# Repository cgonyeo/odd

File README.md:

odd
===

One Dimensional Display

http://blog.gonyeo.com/category/odd.html

This project aims to create a single row of RGB LEDs that can be individually 
controlled by a Raspberry Pi. The Pi will be able to display single colors, 
basic hardcoded animations, dynamic animations (like audio visualization), and 
animations in reaction to various events (like someone entered a room, or the 
user reveived a message on Facebook).

The hardware will consist of packages of one TLC5947, eight RGB LEDs, one 
voltage regulator, and some capacitors and resistors on a PCB. These circuit 
boards will be daisy chainable, with an end goal of about 30 boards (240 LEDs).

The hardware will be controlled in roughly the following fashion:

HTML/CSS/Javascript ---> C ---> TLC5947 ---> LEDs

Here's an imcomplete parts list:
 - Raspberry Pi
 - TLC5947 (LED Driver)
 - RGB LEDs (8x the # of TLCs)
 - One of the PCBs from the eagle board folder for each TLC
 - Resistors & capacitors
 - LM3940 (Voltage Regulator)

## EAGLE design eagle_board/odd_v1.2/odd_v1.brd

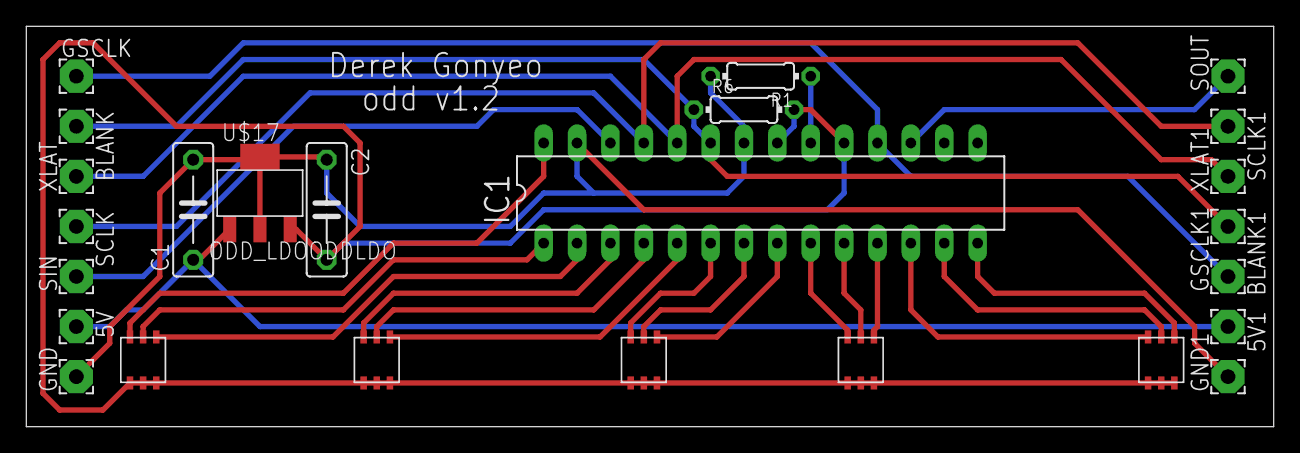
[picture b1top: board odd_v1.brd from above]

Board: 2 copper layers, 94.9 x 30.5 mm, 25 parts (0 on the bottom side), 25 nets.

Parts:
5V, 5V1: 2,54/1,1
BLANK, BLANK1: 2,54/1,1
C1, C2: C075-032X103
GND, GND1: 2,54/1,1
GSCLK, GSCLK1: 2,54/1,1
IC1: DIP28
R1, R6: 0204/7
SCLK, SCLK1: 2,54/1,1
SIN: 2,54/1,1
SOUT: 2,54/1,1
U$1, U$2, U$3, U$4, U$5: RGBLED; 6PADSMD
U$17: ODD_LDOODDLDO; 4PINLDO
XLAT, XLAT1: 2,54/1,1

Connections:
unnamed: IC1.28, U$1.B-
unnamed: IC1.1, U$1.G-
unnamed: IC1.2, U$1.R-
unnamed: IC1.3, U$2.B-
unnamed: IC1.4, U$2.G-
unnamed: IC1.5, U$2.R-
unnamed: IC1.6, U$3.B-
unnamed: IC1.7, U$3.G-
unnamed: IC1.8, U$3.R-
unnamed: IC1.26, SIN.1
unnamed: IC1.14, U$5.R-
unnamed: IC1.13, U$5.G-
unnamed: IC1.12, U$5.B-
unnamed: IC1.11, U$4.R-
unnamed: IC1.10, U$4.G-
unnamed: IC1.9, U$4.B-
unnamed: IC1.25, SCLK.1, SCLK1.1
unnamed: 5V.1, 5V1.1, C1.1, U$17.INPUT
unnamed: C1.2, C2.1, GND.1, GND1.1, IC1.22, IC1.27, R1.2, U$17.GND, U$17.GND2
unnamed: IC1.24, XLAT.1, XLAT1.1
unnamed: GSCLK.1, GSCLK1.1, IC1.18
unnamed: C2.2, IC1.19, IC1.21, R6.2, U$1.B+, U$1.G+, U$1.R+, U$2.B+, U$2.G+, U$2.R+, U$3.B+, U$3.G+, U$3.R+, U$4.B+, U$4.G+, U$4.R+, U$5.B+, U$5.G+, U$5.R+, U$17.OUTPUT
unnamed: IC1.17, SOUT.1
unnamed: BLANK.1, BLANK1.1, IC1.23, R6.1
unnamed: IC1.20, R1.1

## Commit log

2013-02-17 Initial commit. Proof of concept, arduino receives information from computer and updates LEDs to show a basic animation.
2013-02-17 Added an incomplete eagle board.
2013-02-17 Updated board, all desired connections in schematic have been made.
2013-02-18 Schematic modified to only have one TLC590, board made.
2013-02-18 Label added to board.
2013-02-18 Small changes.
2013-02-18 Made the cylonEye animation smoother
2013-02-18 Modified board, there were accidental and dumb connections being made. Also added two capacitors for use with the voltage regulator.
2013-02-19 Modified code to function with two Tlc5940s. Need to add capacitors to prevent decoupling issues to circuit, and then switch back off of bit banging to talk to the ics
2013-02-19 Added a strobe method
2013-02-19 Added threading support and fixed a potential bug with the serial writing. Baud rate also halved.
2013-02-19 LEDs were off by two. Fixed it. Not sure why that was happening or why my fix fixed it, but it fixed it.
2013-02-19 An LED wasn't updating because I told it not to. Removed the code that was doing that.
2013-02-19 Added ability for user input
2013-02-27 Made removing process easier (had to hit enter too many times). Also renamed file.
2013-02-27 Fixed stuff, added smoothStrobe animation
2013-02-27 Updated the board
2013-02-27 Added some animations
2013-02-28 Added initial color support. Not yet available to user.
2013-03-04 Added an inverse subtract, and fixed bug causing segmentation faults when the arduino is unplugged than the program is exited.
2013-03-05 Added a sin animation
2013-03-27 This commit might break lots of stuff. Need to back it up though.
2013-03-30 Full color support added, some animations appear broken.
2013-03-30 Color support fully functional
2013-04-01 C driver has been split up into multiple files for better organization, and it now replies on another program to pass it instructions over the network.
2013-04-01 Removed files I never meant to commit, and included Python Websocket -> Socket program (to be used with javascript).
2013-04-01 Didn't mean to commit these either...
2013-04-02 LEDs are now ontrollable from a website
2013-04-03 Fixed a bug in the arduino code that prevented a channel from updating when daisy chaining the pcbs, (maybe) fixed a time overflow error when running long enough, and fixed a javascript error when en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
2013-04-03 Initial audio support implemented. 3/4 of a second of a lag exists between the computer and the LEDs, so the arduino will need to be removed completely. The driver for the TLC5940s will be rewritten 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
2013-04-07 Website UI significantly improved. Probably didn't break functionality.
2013-04-09 Updated README to reflect pending removal of the Arduino
2013-04-09 Added a new version of the board, it's now easier to daisy chain and cheaper
2013-04-11 Working on moving over to Raspberry Pi, driver for the TLC5940 currently doesn't work, and thus LEDs are mostly unusable
2013-04-16 Moved around components on the board to make some paths shorter
2013-04-17 Advanced page creation started. Needs more Javascript.
2013-04-18 deleting some unneeded files
2013-04-22 Updates and stuff
2013-04-22 Advanced page now shows currently running animations on load
2013-04-25 Added a little error checking
2013-04-26 Moved to the tlc5947
2013-04-30 Changed file names to reflect the new chip
2013-05-02 Audio now works. Basic volume based animation functioning. Updated README.
2013-05-04 FFTs are now being run. Still figuring out how to work with their outputs.
2013-05-06 Modified a couple numbers, it now works a lot better.
2013-06-30 This commit will break many things
2013-07-08 More broken code
2013-08-24 Rob fixes things, networking disabled to prevent segfaults.
2014-01-31 Changing networking, moved things too odd.h
2014-01-31 Nuked the website
2014-02-04 It is now possible to add animations via the network
2014-02-06 More networking goodness
2014-02-06 Flask server beginnings
2014-02-06 ls action now functioning
2014-02-12 Added the Game Of Life as an animation
2014-03-05 Moved from jack to alsa for sound
2014-04-09 Pushing without testing, lol. Added cycle, cleaned up cylon eye.
2014-04-11 Fixed cycle/dammit, cleaned up cyloneye
2014-04-23 Added wave animation, incomplete rain animation
